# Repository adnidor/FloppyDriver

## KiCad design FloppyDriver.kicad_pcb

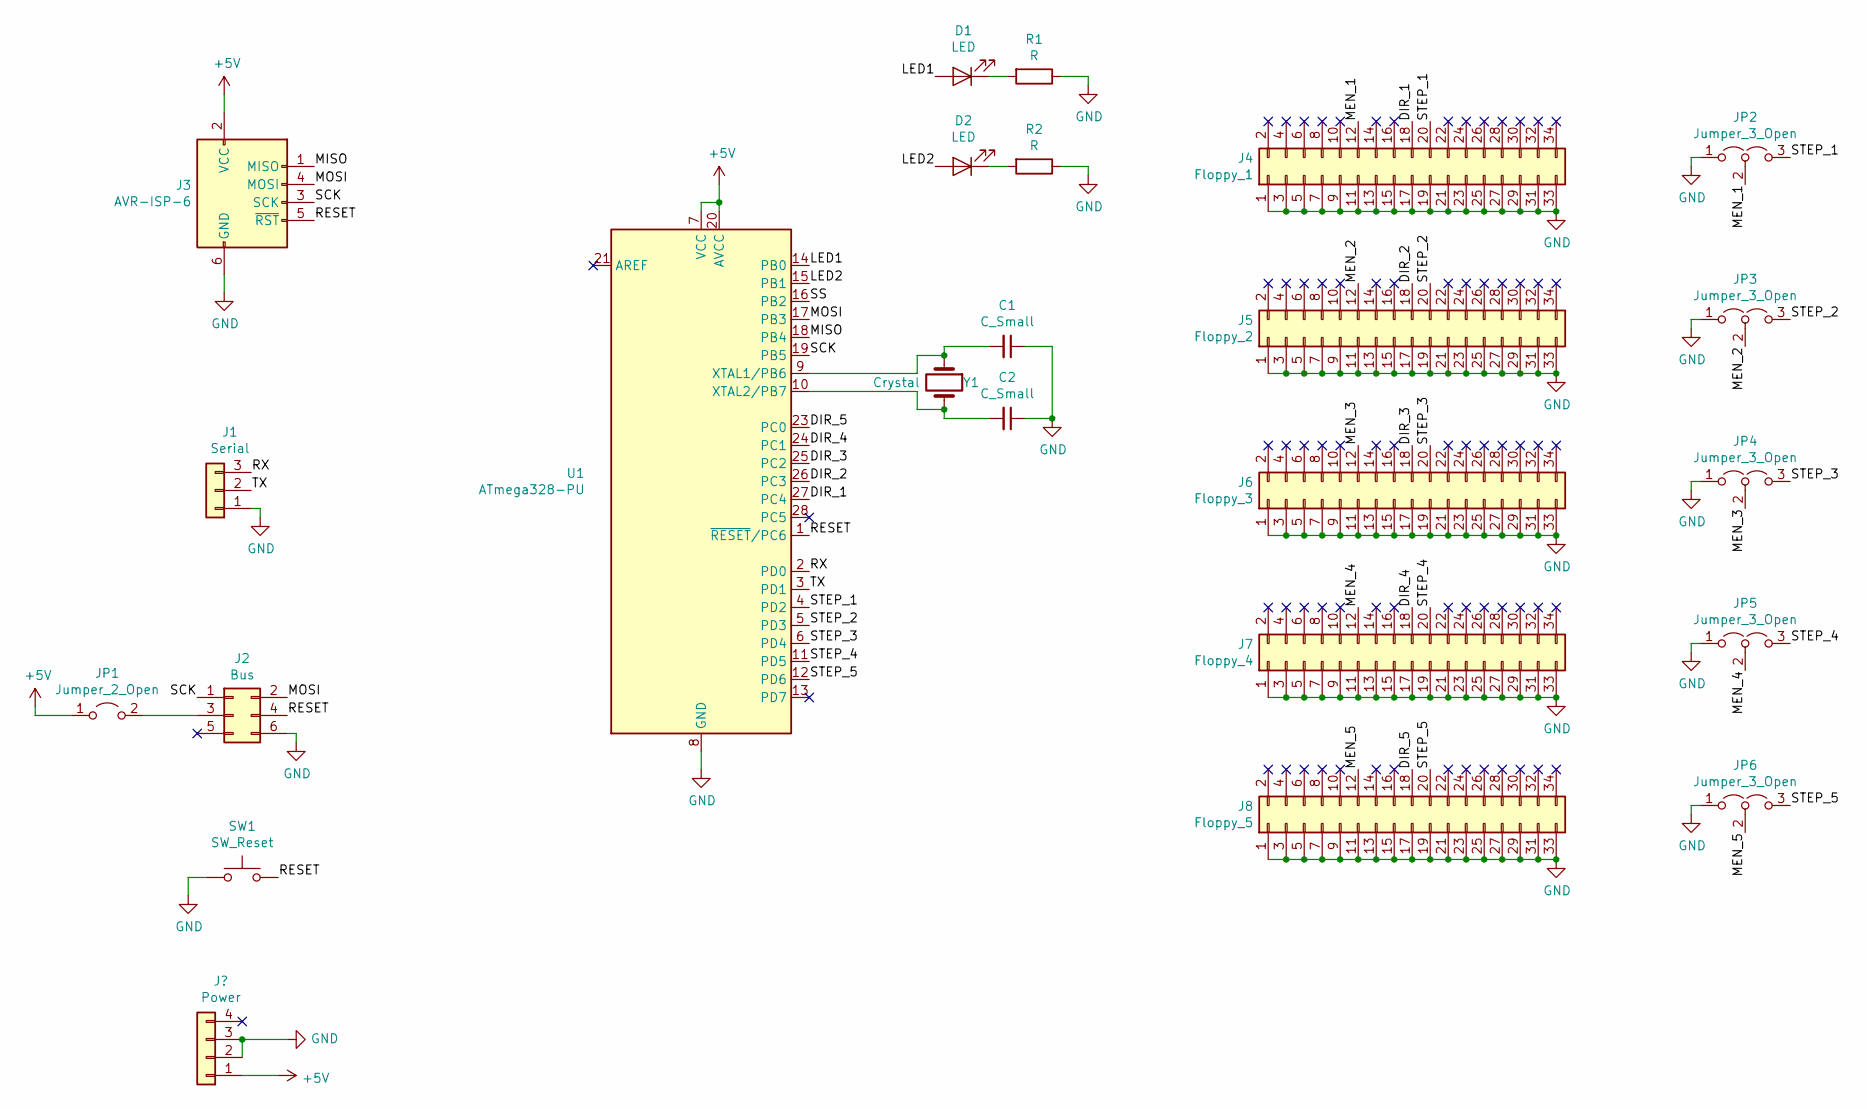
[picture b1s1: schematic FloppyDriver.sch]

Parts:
C1, C2: C_Small; C_Disc_D5.0mm_W2.5mm_P2.50mm
D1, D2: LED; LED_D5.0mm
J1: Serial; PinHeader_1x03_P2.54mm_Vertical
J2: Bus; IDC-Header_2x03_P2.54mm_Vertical
J3: AVR-ISP-6; IDC-Header_2x03_P2.54mm_Vertical
J4: Floppy_1; IDC-Header_2x17_P2.54mm_Vertical
J5: Floppy_2; IDC-Header_2x17_P2.54mm_Vertical
J6: Floppy_3; IDC-Header_2x17_P2.54mm_Vertical
J7: Floppy_4; IDC-Header_2x17_P2.54mm_Vertical
J8: Floppy_5; IDC-Header_2x17_P2.54mm_Vertical
JP1: Jumper_2_Open; PinHeader_1x02_P2.54mm_Vertical
JP2, JP3, JP4, JP5, JP6: Jumper_3_Open; PinHeader_1x03_P2.54mm_Vertical
R1, R2: R; R_Axial_DIN0207_L6.3mm_D2.5mm_P10.16mm_Horizontal
SW1: SW_Reset; SW_PUSH_6mm
U1: ATmega328-PU; DIP-28_W7.62mm
Y1: Crystal; Crystal_HC49-U_Vertical

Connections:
+5V: J3.2 (VCC), JP1.1 (A), U1.7 (VCC), U1.20 (AVCC); also elsewhere on the board
/DIR_1: J4.18, U1.27 (PC4)
/DIR_2: J5.18, U1.26 (PC3)
/DIR_3: J6.18, U1.25 (PC2)
/DIR_4: J7.18, U1.24 (PC1)
/DIR_5: J8.18, U1.23 (PC0)
/LED1: D1.2 (A), U1.14 (PB0)
/LED2: D2.2 (A), U1.15 (PB1)
/MEN_1: J4.12, JP2.2 (C)
/MEN_2: J5.12, JP3.2 (C)
/MEN_3: J6.12, JP4.2 (C)
/MEN_4: J7.12, JP5.2 (C)
/MEN_5: J8.12, JP6.2 (C)
/MISO: J3.1 (MISO), U1.18 (PB4)
/MOSI: J2.2, J3.4 (MOSI), U1.17 (PB3)
/RESET: J2.4, J3.5 (~RST), SW1.2, U1.1 (~RESET~/PC6)
/RX: J1.3, U1.2 (PD0)
/SCK: J2.1, J3.3 (SCK), U1.19 (PB5)
/SS: U1.16 (PB2)
/STEP_1: J4.20, JP2.3 (B), U1.4 (PD2)
/STEP_2: J5.20, JP3.3 (B), U1.5 (PD3)
/STEP_3: J6.20, JP4.3 (B), U1.6 (PD4)
/STEP_4: J7.20, JP5.3 (B), U1.11 (PD5)
/STEP_5: J8.20, JP6.3 (B), U1.12 (PD6)
/TX: J1.2, U1.3 (PD1)
GND: C1.1, C2.1, J1.1, J2.6, J3.6 (GND), J4.1, J4.3, J4.5, J4.7, J4.9, J4.11, J4.13, J4.15, J4.17, J4.19, J4.21, J4.23, J4.25, J4.27, J4.29, J4.31, J4.33, J5.1, J5.3, J5.5, J5.7, J5.9, J5.11, J5.13, J5.15, J5.17, J5.19, J5.21, J5.23, J5.25, J5.27, J5.29, J5.31, J5.33, J6.1, J6.3, J6.5, J6.7, J6.9, J6.11, J6.13, J6.15, J6.17, J6.19, J6.21, J6.23, J6.25, J6.27, J6.29, J6.31, J6.33, J7.1, J7.3, J7.5, J7.7, J7.9, J7.11, J7.13, J7.15, J7.17, J7.19, J7.21, J7.23, J7.25, J7.27, J7.29, J7.31, J7.33, J8.1, J8.3, J8.5, J8.7, J8.9, J8.11, J8.13, J8.15, J8.17, J8.19, J8.21, J8.23, J8.25, J8.27, J8.29, J8.31, J8.33, JP2.1 (A), JP3.1 (A), JP4.1 (A), JP5.1 (A), JP6.1 (A), R1.1, R2.1, SW1.1, U1.8 (GND), U1.22 (GND); also elsewhere on the board
unnamed: C1.2, U1.9 (XTAL1/PB6), Y1.1
unnamed: C2.2, U1.10 (XTAL2/PB7), Y1.2
unnamed: D1.1 (K), R1.2
unnamed: D2.1 (K), R2.2
unnamed: J2.3, JP1.2 (B)

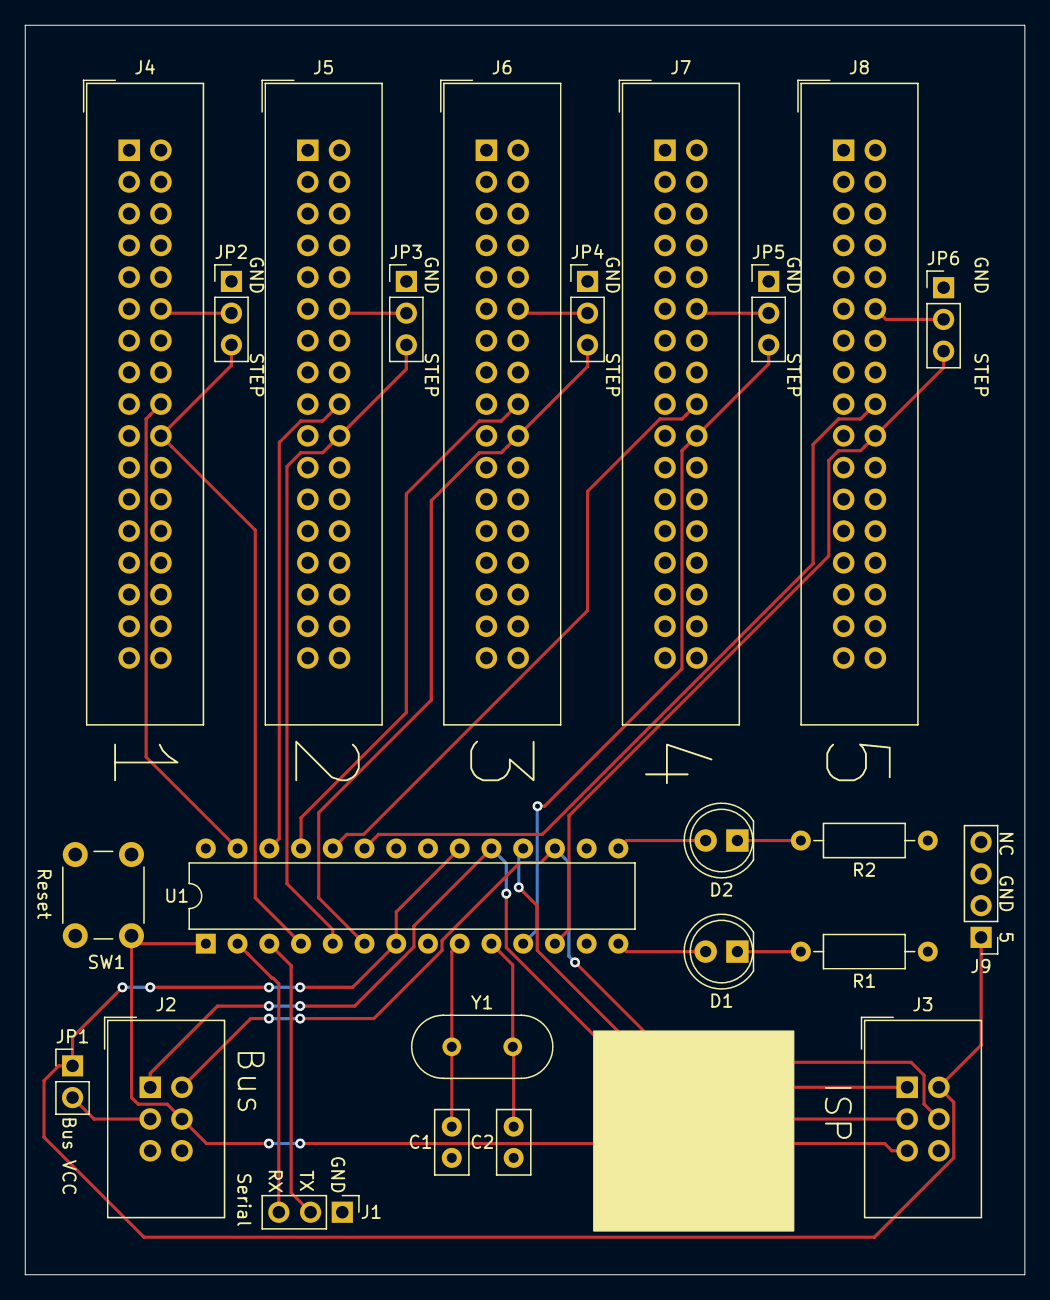
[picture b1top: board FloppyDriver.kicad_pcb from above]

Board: 2 copper layers, 80.0 x 100.0 mm, 24 parts (0 on the bottom side), 30 nets.

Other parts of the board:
J9: Power; PinHeader_1x04_P2.54mm_Vertical

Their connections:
+5V: J9.1; also elsewhere on the board
GND: J9.2, J9.3; also elsewhere on the board

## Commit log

2019-08-10 init
